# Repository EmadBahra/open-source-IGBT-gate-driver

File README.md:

# Please read Wiki it will be complete ASAP
##  This is a beta version and it's not tested yet, so use it at your own risk under GPL v3 

##  Features
1. Short pulse suppression
2. Under voltage protection
3. Fault soft turn off
4. Active auto reset dynamic VCE clamp
5. Separate Ron and Roff
6. VCE monitoring
7. High side-Low side shoot thought protection (not tested yet)
8. Adjustable VCE protection
9. Mosfet gate clamp

## To add:
1. dynamic short-circuit protection
2. Designing its own converter

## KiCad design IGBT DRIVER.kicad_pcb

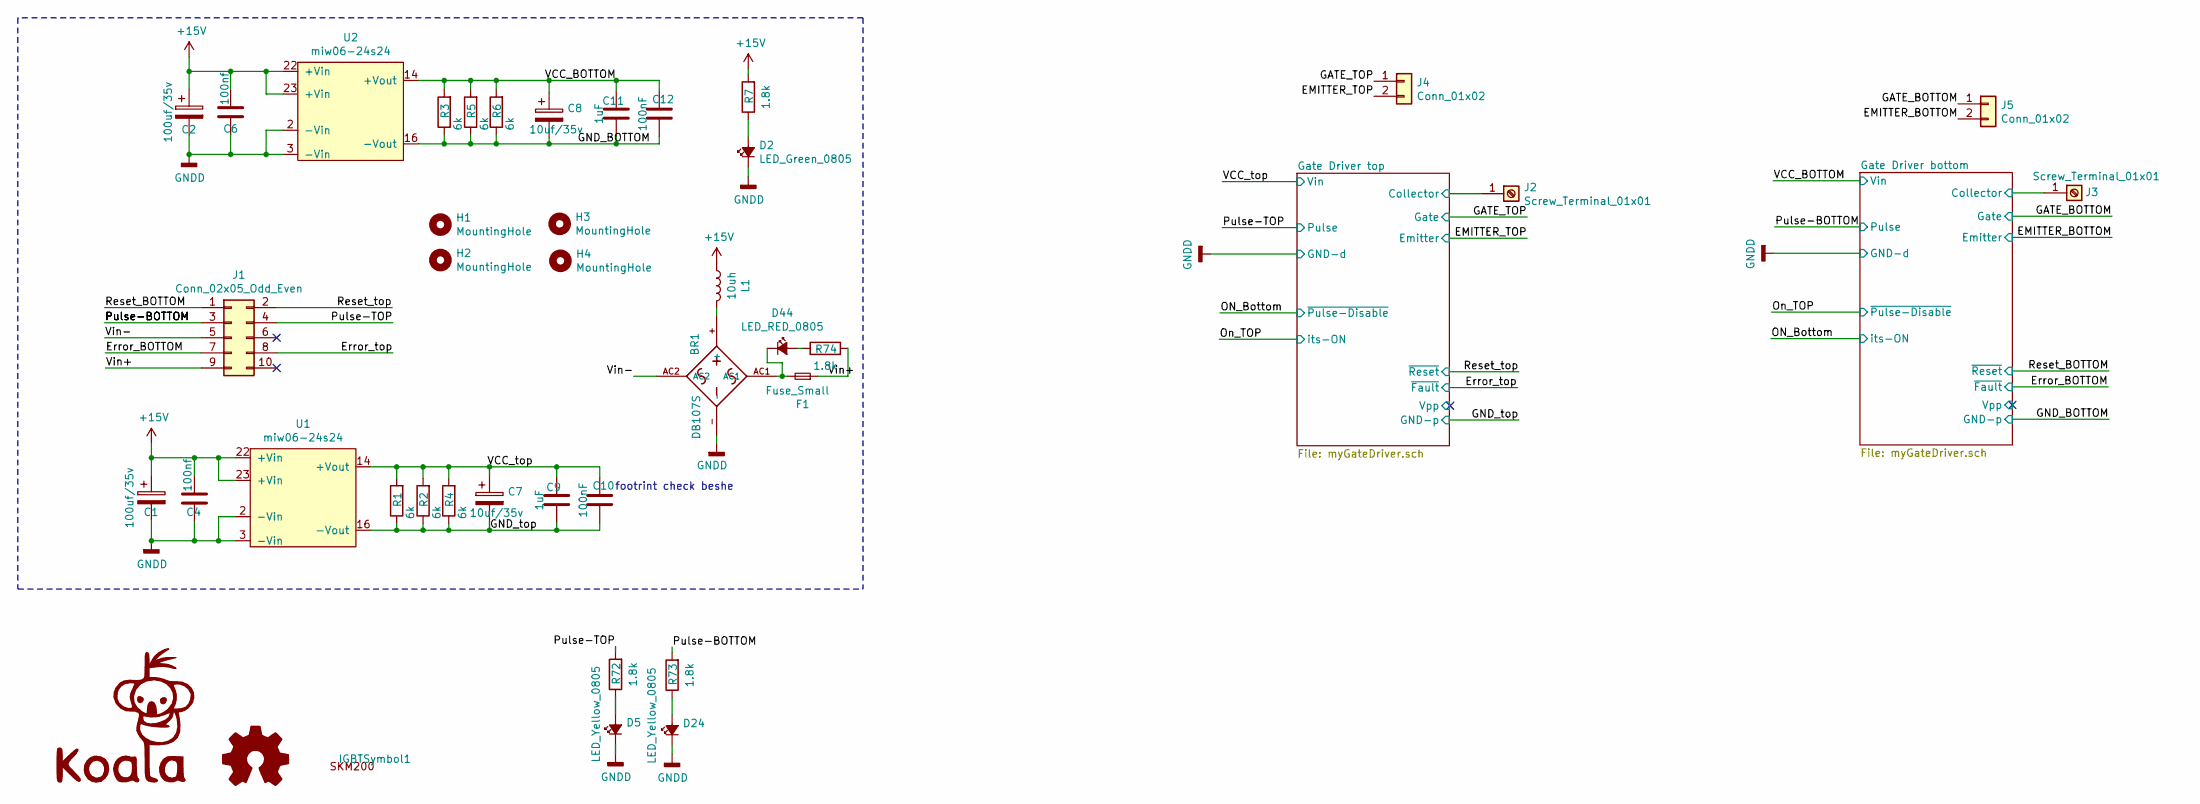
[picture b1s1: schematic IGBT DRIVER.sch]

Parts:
BR1: DB107S; DIOB_DB107S
C1, C2: 100uf/35v; CP_Radial_D6.3mm_P2.50mm
C4, C6: 100nf; C_1206_3216Metric_Pad1.33x1.80mm_HandSolder
C7, C8: 10uf/35v; CP_Radial_D5.0mm_P2.50mm
C9, C11: 1uF; C_1206_3216Metric_Pad1.33x1.80mm_HandSolder
C10, C12: 100nF; C_1206_3216Metric_Pad1.33x1.80mm_HandSolder
D2: LED_Green_0805
D5, D24: LED_Yellow_0805
D44: LED_RED_0805
F1: Fuse_Small; fuse.holder.1808
G1: LOGO; koalaLogo
H1, H2, H3, H4: MountingHole; MountingHole_4.3x6.2mm_M4_Pad_Via
IGBTSymbol1: SYM_Arrow45_Normal; skm200GB
J1: Conn_02x05_Odd_Even; IDC-Header_2x05-1MP_P2.54mm_Latch_Horizontal
J2, J3: Screw_Terminal_01x01; COOLERI
J4, J5: Conn_01x02; IGBT_Socket
L1: 10uh; L_12x12mm_H6mm
LOGO1: Logo_Open_Hardware_Small; OSHW-Logo_5.7x6mm_SilkScreen
R1, R2, R3, R4, R5, R6: 6k; R_1206_3216Metric
R7, R72, R73, R74: 1.8k; R_0805_2012Metric
U1, U2: miw06-24s24; MIWI06

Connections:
+15V: C1.1, C2.1, C4.2, C6.2, L1.1, R7.2, U1.22 (+Vin), U1.23 (+Vin), U2.22 (+Vin), U2.23 (+Vin); also elsewhere on the board
/EMITTER_BOTTOM: J5.2; also elsewhere on the board
/EMITTER_TOP: J4.2; also elsewhere on the board
/Error_BOTTOM: J1.7; also elsewhere on the board
/Error_top: J1.8; also elsewhere on the board
/GATE_BOTTOM: J5.1; also elsewhere on the board
/GATE_TOP: J4.1; also elsewhere on the board
/GND_BOTTOM: C8.2, C11.1, C12.1, R3.1, R5.1, R6.1, U2.16 (-Vout); also elsewhere on the board
/GND_top: C7.2, C9.1, C10.1, R1.1, R2.1, R4.1, U1.16 (-Vout); also elsewhere on the board
/Gate Driver bottom/Collector: J3.1; also elsewhere on the board
/Gate Driver top/Collector: J2.1; also elsewhere on the board
/Pulse-BOTTOM: J1.3, R73.2; also elsewhere on the board
/Pulse-TOP: J1.4, R72.2; also elsewhere on the board
/Reset_BOTTOM: J1.1; also elsewhere on the board
/Reset_top: J1.2; also elsewhere on the board
/VCC_BOTTOM: C8.1, C11.2, C12.2, R3.2, R5.2, R6.2, U2.14 (+Vout); also elsewhere on the board
/VCC_top: C7.1, C9.2, C10.2, R1.2, R2.2, R4.2, U1.14 (+Vout); also elsewhere on the board
/Vin+: F1.1, J1.9, R74.2
/Vin-: BR1.AC2, J1.5
unnamed: BR1.+, L1.2
unnamed: BR1.AC1, D44.1 (K), F1.2
unnamed: D2.2 (A), R7.1
unnamed: D5.2 (A), R72.1
unnamed: D24.2 (A), R73.1
unnamed: D44.2 (A), R74.1

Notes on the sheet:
footrint check beshe

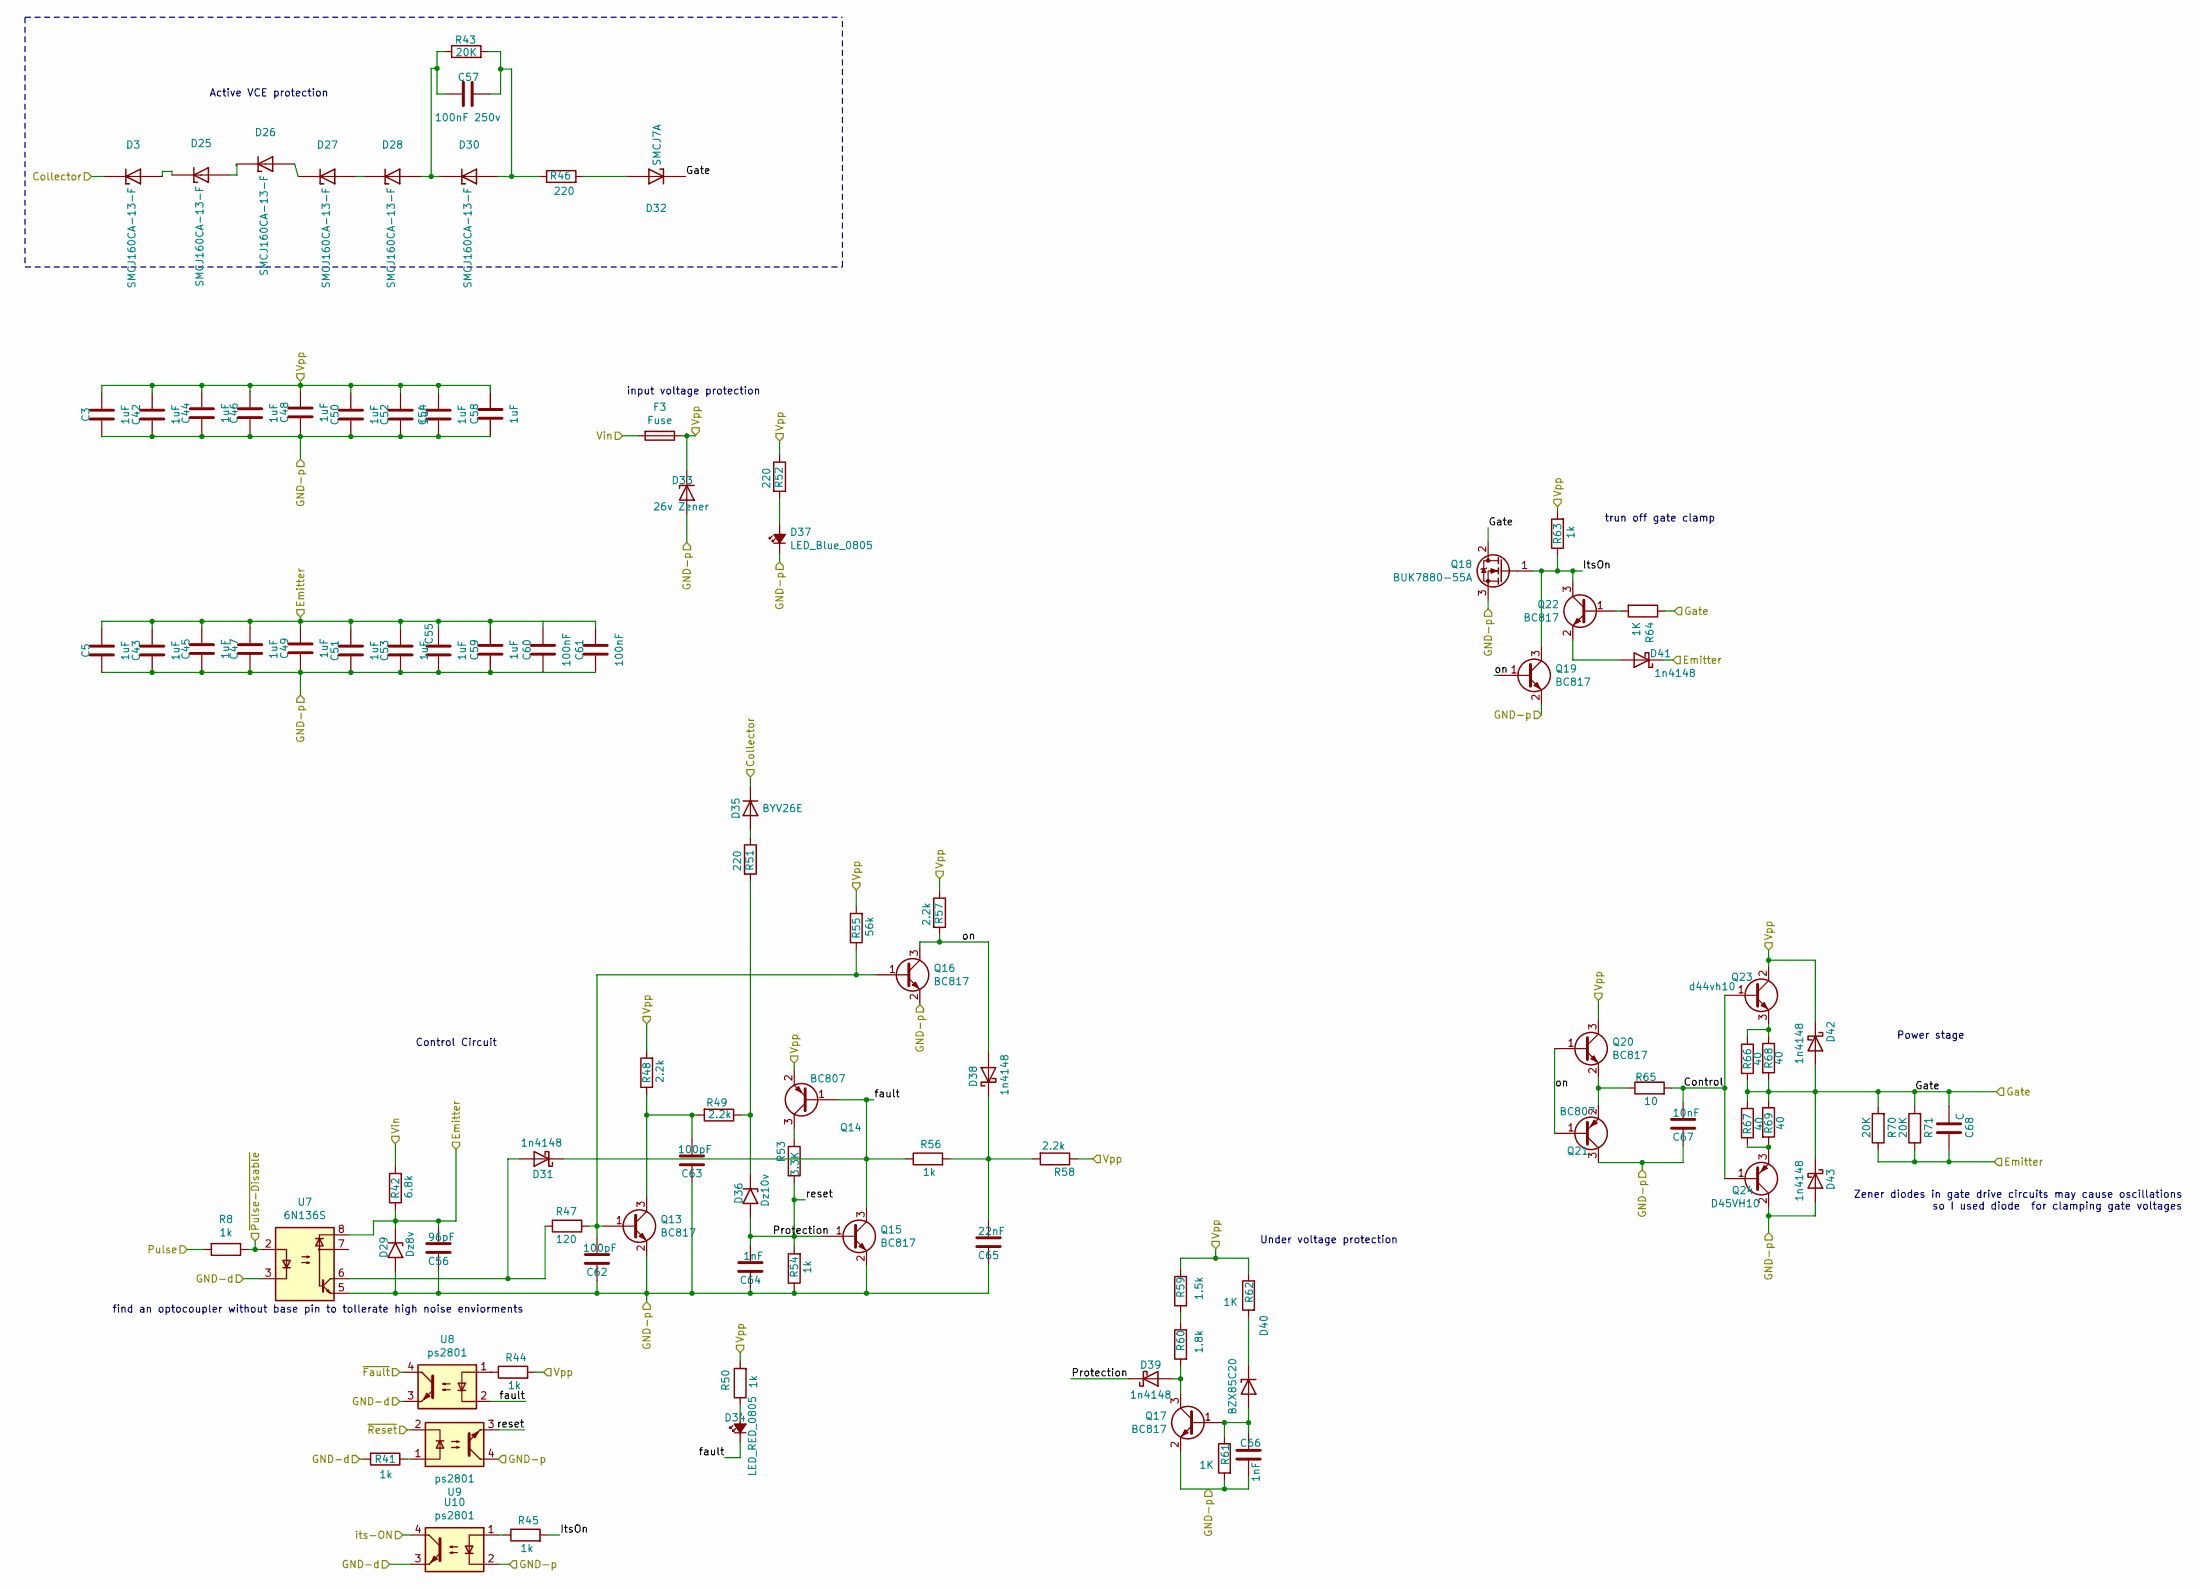
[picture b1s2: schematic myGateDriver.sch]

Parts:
C13, C14, C15, C16, C17, C18, C19, C20, C21, C22, C23, C24, C25, C26, C27, C28, C31, C32: 1uF; C_1206_3216Metric_Pad1.33x1.80mm_HandSolder
C29: 96pF; C_0805_2012Metric
C30: 100nF 250v; C_Rect_L13.0mm_W4.0mm_P10.00mm_FKS3_FKP3_MKS4
C33, C34: 100nF; C_1206_3216Metric_Pad1.33x1.80mm_HandSolder
C35, C36: 100pF; C_0805_2012Metric
C37: 1nF; C_0805_2012Metric
C38: 22nF; C_0805_2012Metric
C39: 1nF; C_1206_3216Metric_Pad1.33x1.80mm_HandSolder
C40: 10nF; C_0805_2012Metric
C41: C; C_0805_2012Metric
D1: LED_RED_0805
D4, D6, D7, D8, D9, D11: SMCJ160CA-13-F; DIOM7959X250N; PARTREV 5-2
D10: Dz8v; D_MELF
D12, D17, D18, D20, D21, D22: 1n4148; D_SMA
D13: SMCJ7A; DIOM7959X250N; PARTREV 5-2
D14: 26v Zener; D_MELF
D15: BYV26E; D_DO-35_SOD27_P7.62mm_Horizontal
D16: Dz10v; D_MELF
D19: BZX85C20; D_MELF
D23: LED_Blue_0805; LED_BLUE_0805
F2: Fuse; fuse.holder.1808
Q1, Q3, Q4, Q5, Q7, Q8, Q10: BC817; SOT-23
Q2, Q9: BC807; SOT-23
Q6: BUK7880-55A; SOT-223-3_TabPin2
Q11: d44vh10; TO-252-2
Q12: D45VH10; TO-252-2
R9, R10, R13, R14, R21, R23, R30, R40: 1k; R_0805_2012Metric
R11: 6.8k; R_0805_2012Metric
R12: 20K; R_Axial_DIN0207_L6.3mm_D2.5mm_P10.16mm_Horizontal
R15: 220; R_Axial_DIN0207_L6.3mm_D2.5mm_P10.16mm_Horizontal
R16: 120; R_0805_2012Metric
R17, R18, R24, R25: 2.2k; R_0805_2012Metric
R19, R39: 220; R_0805_2012Metric
R20: 3.3K; R_0805_2012Metric
R22: 56k; R_0805_2012Metric
R26: 1.5k; R_0805_2012Metric
R27: 1.8k; R_0805_2012Metric
R28, R29, R31: 1K; R_0805_2012Metric
R32: 10; R_0805_2012Metric
R33, R34, R35, R36: 40; R_2512_6332Metric
R37, R38: 20K; R_0805_2012Metric
U3: 6N136S; SMDIP-8_W9.53mm
U4, U5, U6: ps2801; SOP-4_4.4x2.6mm_P1.27mm

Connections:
/EMITTER_BOTTOM: C14.2, C16.2, C18.2, C20.2, C22.2, C24.2, C26.2, C28.2, C29.2, C32.2, C33.2, C34.2, C41.1, D10.1 (A1), D20.1 (K), R11.1, R37.1, R38.1, U3.8; also elsewhere on the board
/Error_BOTTOM: U4.4; also elsewhere on the board
/GATE_BOTTOM: C41.2, D13.C, D21.2 (A), D22.1 (K), Q6.2 (D), R31.1, R33.2, R34.1, R35.2, R36.1, R37.2, R38.2; also elsewhere on the board
/GND_BOTTOM: C13.1, C14.1, C15.1, C16.1, C17.1, C18.1, C19.1, C20.1, C21.1, C22.1, C23.1, C24.1, C25.1, C26.1, C27.1, C28.1, C29.1, C31.1, C32.1, C33.1, C34.1, C35.1, C36.1, C37.1, C38.1, C39.2, C40.1, D10.2 (A2), D14.2 (A), D22.2 (A), D23.1 (K), Q1.2 (E), Q3.2 (E), Q4.2 (E), Q5.2 (E), Q6.3 (S), Q7.2 (E), Q9.3 (C), Q12.2 (C), R21.1, R28.2, U3.5, U5.4, U6.2; also elsewhere on the board
/Gate Driver bottom/Collector: D4.C, D15.2 (K); also elsewhere on the board
/Gate Driver bottom/Control: C40.2, Q11.1 (B), Q12.1 (B), R32.2
/Gate Driver bottom/ItsOn: Q6.1 (G), Q7.3 (C), Q10.3 (C), R14.2, R30.1
/Gate Driver bottom/Protection: C37.2, D16.2 (A2), D18.1 (K), Q3.1 (B), R20.2, R21.2, U5.3
/Gate Driver bottom/Vpp: C13.2, C15.2, C17.2, C19.2, C21.2, C23.2, C25.2, C27.2, C31.2, D14.1 (K), D21.1 (K), F2.1, Q2.2 (E), Q8.3 (C), Q11.2 (C), R13.2, R17.2, R22.2, R24.1, R25.1, R26.1, R29.1, R30.2, R39.1, R40.2
/Gate Driver bottom/fault: D1.1 (K), D12.1 (K), Q2.1 (B), Q3.3 (C), R23.1, U4.2
/Gate Driver bottom/on: D17.2 (A), Q4.3 (C), Q7.1 (B), Q8.1 (B), Q9.1 (B), R24.2
/ON_Bottom: U6.4; also elsewhere on the board
/On_TOP: R9.1, U3.2; also elsewhere on the board
/Pulse-BOTTOM: R9.2; also elsewhere on the board
/Reset_BOTTOM: U5.2; also elsewhere on the board
/VCC_BOTTOM: F2.2, R11.2; also elsewhere on the board
unnamed: C30.1, D9.A, D11.C, R12.1
unnamed: C30.2, D11.A, R12.2, R15.1
unnamed: C35.2, Q1.1 (B), Q4.1 (B), R16.1, R22.1
unnamed: C36.2, Q1.3 (C), R17.1, R18.2
unnamed: C38.2, D17.1 (K), R23.2, R25.2
unnamed: C39.1, D19.2 (A), Q5.1 (B), R28.1
unnamed: D1.2 (A), R40.1
unnamed: D4.A, D6.C
unnamed: D6.A, D7.C
unnamed: D7.A, D8.C
unnamed: D8.A, D9.C
unnamed: D12.2 (A), R16.2, U3.6
unnamed: D13.A, R15.2
unnamed: D15.1 (A), R19.1
unnamed: D16.1 (A1), R18.1, R19.2
unnamed: D18.2 (A), Q5.3 (C), R27.2
unnamed: D19.1 (K), R29.2
unnamed: D20.2 (A), Q10.2 (E)
unnamed: D23.2 (A), R39.2
unnamed: Q2.3 (C), R20.1
unnamed: Q8.2 (E), Q9.2 (E), R32.1
unnamed: Q10.1 (B), R31.2
unnamed: Q11.3 (E), R33.1, R35.1
unnamed: Q12.3 (E), R34.2, R36.2
unnamed: R10.1, U5.1
unnamed: R13.1, U4.1
unnamed: R14.1, U6.1
unnamed: R26.2, R27.1

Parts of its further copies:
C3, C5, C42, C43, C44, C45, C46, C47, C48, C49, C50, C51, C52, C53, C54, C55, C58, C59: 1uF; C_1206_3216Metric_Pad1.33x1.80mm_HandSolder
C56: 96pF; C_0805_2012Metric
C57: 100nF 250v; C_Rect_L13.0mm_W4.0mm_P10.00mm_FKS3_FKP3_MKS4
C60, C61: 100nF; C_1206_3216Metric_Pad1.33x1.80mm_HandSolder
C62, C63: 100pF; C_0805_2012Metric
C64: 1nF; C_0805_2012Metric
C65: 22nF; C_0805_2012Metric
C66: 1nF; C_1206_3216Metric_Pad1.33x1.80mm_HandSolder
C67: 10nF; C_0805_2012Metric
C68: C; C_0805_2012Metric
D3, D25, D26, D27, D28, D30: SMCJ160CA-13-F; DIOM7959X250N; PARTREV 5-2
D29: Dz8v; D_MELF
D31, D38, D39, D41, D42, D43: 1n4148; D_SMA
D32: SMCJ7A; DIOM7959X250N; PARTREV 5-2
D33: 26v Zener; D_MELF
D34: LED_RED_0805
D35: BYV26E; D_DO-35_SOD27_P7.62mm_Horizontal
D36: Dz10v; D_MELF
D37: LED_Blue_0805; LED_BLUE_0805
D40: BZX85C20; D_MELF
F3: Fuse; fuse.holder.1808
Q13, Q15, Q16, Q17, Q19, Q20, Q22: BC817; SOT-23
Q14, Q21: BC807; SOT-23
Q18: BUK7880-55A; SOT-223-3_TabPin2
Q23: d44vh10; TO-252-2
Q24: D45VH10; TO-252-2
R8, R41, R44, R45, R50, R54, R56, R63: 1k; R_0805_2012Metric
R42: 6.8k; R_0805_2012Metric
R43: 20K; R_Axial_DIN0207_L6.3mm_D2.5mm_P10.16mm_Horizontal
R46: 220; R_Axial_DIN0207_L6.3mm_D2.5mm_P10.16mm_Horizontal
R47: 120; R_0805_2012Metric
R48, R49, R57, R58: 2.2k; R_0805_2012Metric
R51, R52: 220; R_0805_2012Metric
R53: 3.3K; R_0805_2012Metric
R55: 56k; R_0805_2012Metric
R59: 1.5k; R_0805_2012Metric
R60: 1.8k; R_0805_2012Metric
R61, R62, R64: 1K; R_0805_2012Metric
R65: 10; R_0805_2012Metric
R66, R67, R68, R69: 40; R_2512_6332Metric
R70, R71: 20K; R_0805_2012Metric
U7: 6N136S; SMDIP-8_W9.53mm
U8, U9, U10: ps2801; SOP-4_4.4x2.6mm_P1.27mm

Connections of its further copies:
/EMITTER_TOP: C5.2, C43.2, C45.2, C47.2, C49.2, C51.2, C53.2, C55.2, C56.2, C59.2, C60.2, C61.2, C68.1, D29.1 (A1), D41.1 (K), R42.1, R70.1, R71.1, U7.8; also elsewhere on the board
/Error_top: U8.4; also elsewhere on the board
/GATE_TOP: C68.2, D32.C, D42.2 (A), D43.1 (K), Q18.2 (D), R64.1, R66.2, R67.1, R68.2, R69.1, R70.2, R71.2; also elsewhere on the board
/GND_top: C3.1, C5.1, C42.1, C43.1, C44.1, C45.1, C46.1, C47.1, C48.1, C49.1, C50.1, C51.1, C52.1, C53.1, C54.1, C55.1, C56.1, C58.1, C59.1, C60.1, C61.1, C62.1, C63.1, C64.1, C65.1, C66.2, C67.1, D29.2 (A2), D33.2 (A), D37.1 (K), D43.2 (A), Q13.2 (E), Q15.2 (E), Q16.2 (E), Q17.2 (E), Q18.3 (S), Q19.2 (E), Q21.3 (C), Q24.2 (C), R54.1, R61.2, U7.5, U9.4, U10.2; also elsewhere on the board
/Gate Driver top/Collector: D3.C, D35.2 (K); also elsewhere on the board
/Gate Driver top/Control: C67.2, Q23.1 (B), Q24.1 (B), R65.2
/Gate Driver top/ItsOn: Q18.1 (G), Q19.3 (C), Q22.3 (C), R45.2, R63.1
/Gate Driver top/Protection: C64.2, D36.2 (A2), D39.1 (K), Q15.1 (B), R53.2, R54.2, U9.3
/Gate Driver top/Vpp: C3.2, C42.2, C44.2, C46.2, C48.2, C50.2, C52.2, C54.2, C58.2, D33.1 (K), D42.1 (K), F3.1, Q14.2 (E), Q20.3 (C), Q23.2 (C), R44.2, R48.2, R50.2, R52.1, R55.2, R57.1, R58.1, R59.1, R62.1, R63.2
/Gate Driver top/fault: D31.1 (K), D34.1 (K), Q14.1 (B), Q15.3 (C), R56.1, U8.2
/Gate Driver top/on: D38.2 (A), Q16.3 (C), Q19.1 (B), Q20.1 (B), Q21.1 (B), R57.2
/ON_Bottom: R8.1, U7.2; also elsewhere on the board
/On_TOP: U10.4; also elsewhere on the board
/Pulse-TOP: R8.2; also elsewhere on the board
/Reset_top: U9.2; also elsewhere on the board
/VCC_top: F3.2, R42.2; also elsewhere on the board
unnamed: C57.1, D28.A, D30.C, R43.1
unnamed: C57.2, D30.A, R43.2, R46.1
unnamed: C62.2, Q13.1 (B), Q16.1 (B), R47.1, R55.1
unnamed: C63.2, Q13.3 (C), R48.1, R49.2
unnamed: C65.2, D38.1 (K), R56.2, R58.2
unnamed: C66.1, D40.2 (A), Q17.1 (B), R61.1
unnamed: D25.A, D26.C
unnamed: D3.A, D25.C
unnamed: D26.A, D27.C
unnamed: D27.A, D28.C
unnamed: D31.2 (A), R47.2, U7.6
unnamed: D32.A, R46.2
unnamed: D34.2 (A), R50.1
unnamed: D35.1 (A), R51.1
unnamed: D36.1 (A1), R49.1, R51.2
unnamed: D37.2 (A), R52.2
unnamed: D39.2 (A), Q17.3 (C), R60.2
unnamed: D40.1 (K), R62.2
unnamed: D41.2 (A), Q22.2 (E)
unnamed 78: U7.3; also elsewhere on the board
unnamed: Q14.3 (C), R53.1
unnamed: Q20.2 (E), Q21.2 (E), R65.1
unnamed: Q22.1 (B), R64.2
unnamed: Q23.3 (E), R66.1, R68.1
unnamed: Q24.3 (E), R67.2, R69.2
unnamed: R41.1, U9.1
unnamed: R44.1, U8.1
unnamed: R45.1, U10.1
unnamed: R59.2, R60.1

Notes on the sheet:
Zener diodes in gate drive circuits may cause oscillations so I used diode for clamping gate voltages
Active VCE protection
input voltage protection
trun off gate clamp
Under voltage protection
Power stage
Control Circuit
find an optocoupler without base pin to tollerate high noise enviorments

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
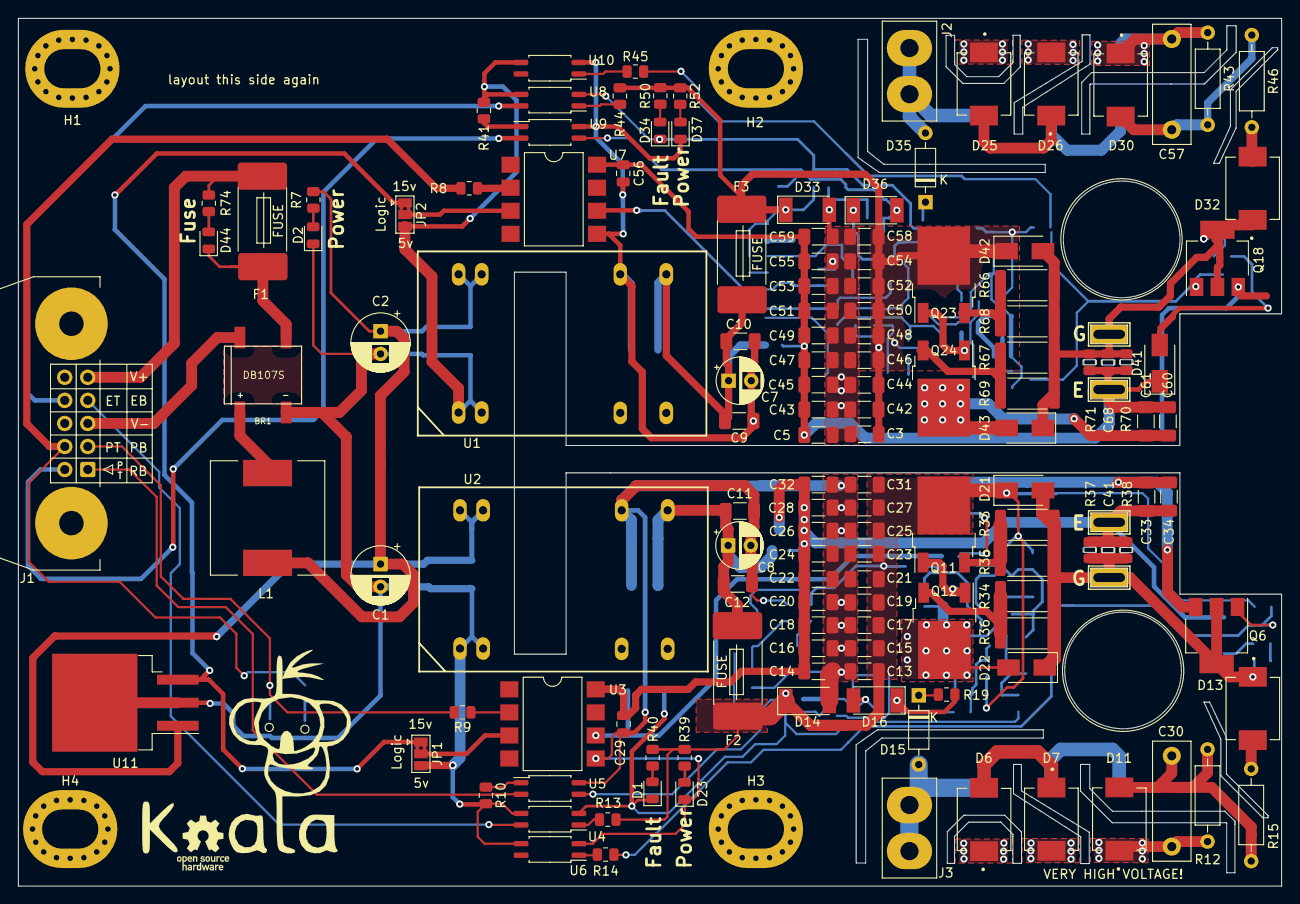
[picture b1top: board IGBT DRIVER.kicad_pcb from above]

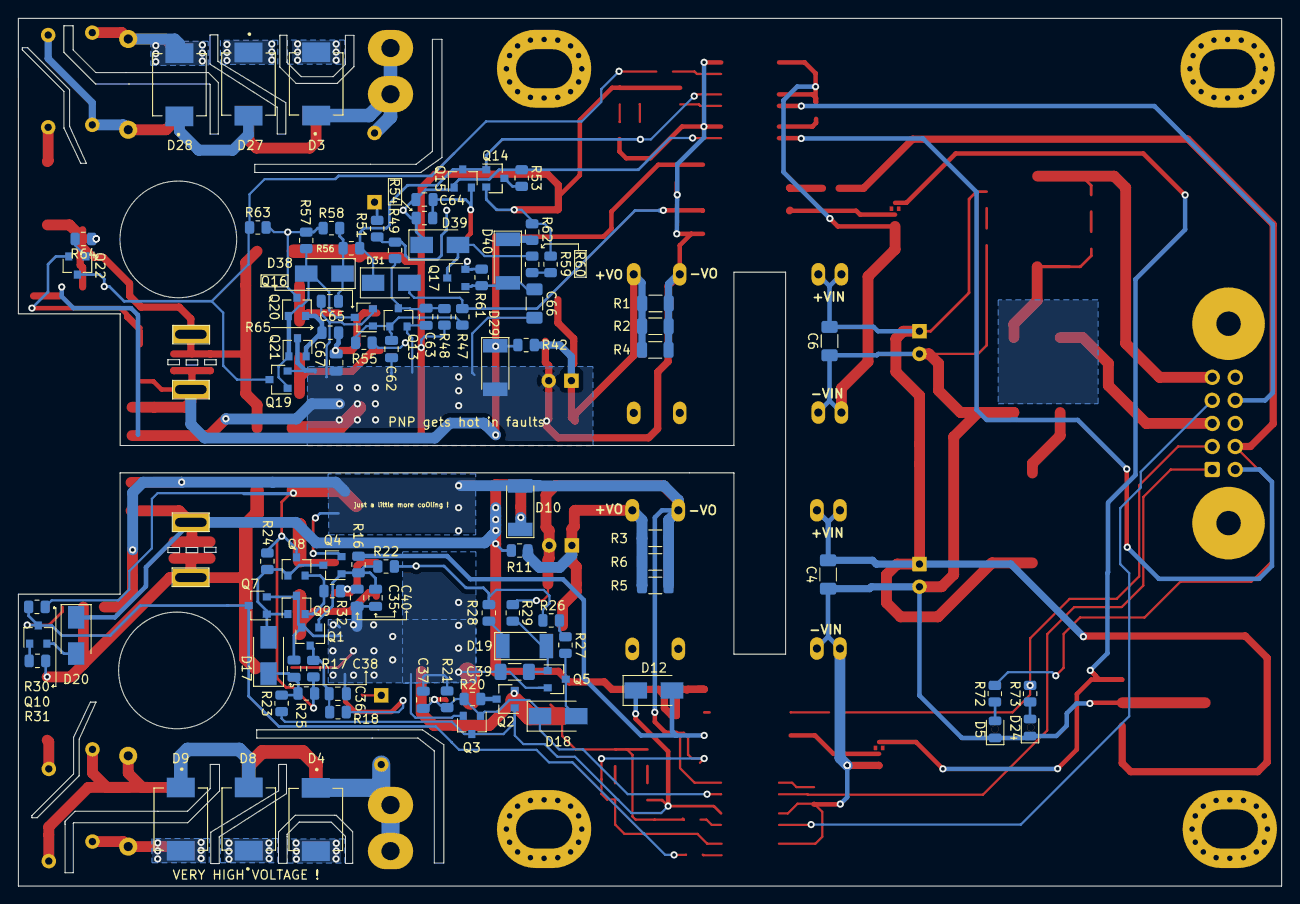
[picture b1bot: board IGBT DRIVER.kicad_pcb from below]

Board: 2 copper layers, 139.2 x 95.6 mm, 240 parts (94 on the bottom side), 99 nets.

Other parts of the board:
JP1, JP2: SolderJumper_3_Bridged12; SolderJumper-3_P1.3mm_Bridged2Bar12_Pad1.0x1.5mm
U11: L7833s(D2pack); TO-263-3_TabPin2

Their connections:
+5V: JP1.1, JP2.1, U11.3
+15V: U11.1; also elsewhere on the board
unnamed 78: JP2.2; also elsewhere on the board

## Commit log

2021-11-15 fuse added
2021-11-15 skm200 layout added
2021-11-15 skm200 3d
2021-11-16 changed bjt
2021-11-16 some placement
2021-11-17 some placements have done
2021-11-18 placing back of bottom
2021-11-22 added top parts
2021-11-23 topside added
2021-11-24 BOM added
2021-11-24 15v logic added
2021-11-24 Set theme jekyll-theme-cayman
2021-11-24 Create CNAME
2021-11-24 Update CNAME
2021-11-26 add some wiki pics
2021-11-26 under voltage picture for wiki
2021-11-26 soft shutdown wiki pic added
2021-11-26 skm200 tpsc pic added
2021-11-26 soft shutdown picture is changed
2021-11-27 clamping pictures
2021-11-27 clamping video added
2021-12-01 ignore rescue lib
2021-12-30 video added
